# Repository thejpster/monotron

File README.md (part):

# Monotron.

> A simple 1980's home computer style application for the Tiva-C Launchpad

## The Monotron is no more

Monotron was fun, but it was only ever a tech demo rather than something we could build on. Check out <https://github.com/neotron-compute/> for our new family of ARM-based, Rust-powered home computers. 

## Introduction

Monotron is powered by a Texas Instruments TM4C123 microcontroller, containing
an ARM Cortex-M4 core and a number of peripherals. This processor was chosen
because it is available on an inexpensive dev-kit - the Tiva-C Launchpad - and
I happened to have some lying around. The challenge I set myself was, how much
can you squeeze out of this tiny CPU? And can you do it all in pure-Rust?

[See Monotron in Action!](https://www.youtube.com/watch?v=7x_92PXKSN4)

## The Future

Monotron has been replaced by the [Neotron 32](https://github.com/neotron-compute/Neotron-32-Hardware), part of the [Neotron family](https://neotron-compute.github.io). All future work will happen under the Neotron banner, and this repo is in archive mode.

## Features

* 800x600 8-colour VGA output
* 32 KiB SRAM (24 KiB usable for applications)
* 256 KiB Flash ROM
* Choice of low-memory 48x36 text display mode or full 384x288 bitmap graphics mode
* 8-bit mono audio output with 3 channel, 4 waveform synthesiser
* USB Serial I/O
* Atari 9-pin joystick interface
* Simple command-line interface
* I2C expansion interface
* Loadable apps
* Battery backed real-time clock*
* 25-pin IBM PC style parallel printer port*
* MIDI In, Out and Through*
* PS/2 Keyboard and Mouse*
* RS-232 Serial port*
* Watch this space!

 _* Requires additional hardware, included on the [Monotron PCB](#monotron-pcb)_

## Video

Monotron generates an 800x600 VGA video signal at 60 Hz using three SPI
peripherals and a timer to generate the horizontal sync signals. It can do
this because the VGA signal has a pixel clock of 40 MHz and the Tiva-C
Launchpad's TM4C123 CPU runs at 80 MHz. We save on the number of pixels we
have to push through the SPIs by running at half-resolution horizontally
(giving 400x600), which also halves the pixel clock to 20 MHz. I did try 40
MHz mode and it didn't work.

Monotron has two 'modes' it can display on this VGA output.

### Text Mode

Text Mode has a 48 character by 36 line display. Each character cell is 8
pixels wide and 16 pixels high and can take any character from the 8-bit [MS-
DOS Code Page 850](https://en.wikipedia.org/wiki/Code_page_850) character set,
and can have any foreground and background colour from the supported set:

* White
* Red
* Yellow
* Green
* Cyan
* Blue
* Magenta
* Black

The text buffer takes up `48 x 36 x 2 = 3,456` bytes of SRAM.

The built-in font is taken from
[FreeBSD](http://web.mit.edu/freebsd/head/share/syscons/fonts/cp850-8x16.fnt).
There's also a second font which implements Teletext block graphics (or
'sixels').

Any line of text can be displayed in "double height" mode, showing either the
top-half or bottom-half.

Finally, the display is framed with an 8 pixel border at the sides and a 12
pixel border at the top and bottom, to make everything fit neatly and to help
with any minor overscan issues if you use an actual CRT monitor.

### Graphics Mode

Graphics Mode can be enabled and disabled at run-time. It's not enabled by
default because bitmap graphics take up a lot of RAM!

You can attach a 1-bit-per-pixel graphics buffer that is some multiple of 384
pixels (i.e. 384 bits or 48 bytes) long. This buffer is displayed using line-
doubling (i.e. every line is shown twice) so you can go up to 384x288
resolution maximum, which will fill the screen. Each bit from the bitmap is
coloured according to the text cell (see above) it sits on top of, much like a
ZX Spectrum. A full-screen bitmap therefore uses the 3,456 bytes of SRAM from
text-mode plus an additional `384x288 / 8 = 13,824` bytes of SRAM.

## Compiling

You will need to build using Rust Nightly, as we need various experimental
features for Embedded development that are not yet available in Stable.

```
$ rustup toolchain install nightly
$ git clone https://github.com/thejpster/monotron.git
$ cd monotron
$ rustup override set nightly
$ rustup target add thumbv7em-none-eabihf
$ cargo build --release
```

To program the board, you can use lm4flash:

```
$ cargo build --release
$ arm-none-eabi-objcopy -O binary ./target/thumbv7em-none-eabihf/release/monotron ./target/thumbv7em-none-eabihf/release/monotron.bin
$ lm4flash ./target/thumbv7em-none-eabihf/release/monotron.bin
```

Or you can debug in GDB (which will automatically load the program first):

```
$ openocd
<switch to a different terminal>
$ cargo run --release
```

OpenOCD should read our `openocd.cfg` file, which directs it to use the
correct configuration. You may need to run `sudo openocd` if your user doesn't
have permission to open the USB device.

To exit GDB, you may need to press Ctrl-C multiple
times, as it seems it can get a bit stuck.

## Connecting

You have two options when running a Monotron.

1. You can take a bare Tiva-C Launchpad and wire up various connectors using
   the pin-outs in the following sections.
2. You can skip all that make yourself a [Monotron PCB](#monotron-pcb)!

### VGA

Your VGA connector requires five wires:

* Pin 1: Red - connect to PF1 via a 330 Ohm resistor.
* Pin 2: Green - connect to PB7 via a 330 Ohm resistor.
* Pin 3: Blue - connect to PD3 via a 330 Ohm resistor.
* Pin 5: Ground - connect to GND
* Pin 6: Red Return - connect to GND
* Pin 7: Green Return - connect to GND
* Pin 8: Blue Return - connect to GND
* Pin 13: H-Sync - connect to PB4
* Pin 14: V-Sync - connect to PB5

I'm using this arrangement using random resistors I found on my desk, and it
works for me (although the picture is a bit dim, as it actually produces about
0.6V peak rather than 0.7V):

```
-----+
     |     +------+ 330 Ohm        Co-ax in the VGA cable
PB7 o+-----|      |------------(o)==================)+
     |     +------+                                  |
-----+                                               |
                                                    +-+
                                                    | |
                                                    | | 75 Ohm
                                                    | | (in Monitor)
                                                    +-+
                                                     |
                                                     o
                                                    GND
```

The 330 Ohm resistor forms a resistive divider with the 75 Ohm resistor in the
monitor. This is needed to drop the 3.3V output down to 0.7V. Some monitors
are more tolerant of over voltage than others. The higher the resistor you
use, the less current you pulling out of the GPIO pin (we're just over 8mA
currently, which is a bit high) but the lower the voltage the monitor will see
and the dimmer your picture will be. Conversely if you lower the resistor,
more current will flow but it'll be a brigher picture. I'd save your chip from
damage and just wind the brightness control up!

Obviously only one channel is shown above - wire up the blue and red channels
in exactly the same fashion. Finally, don't forget to keep your wires short!
You will have noise if you try and send a 20 MHz signal down 10cm of
unshielded wire.

In a perfect world, your board would offer a 75 ohm source impendance matching
the monitor's 75 ohm impedance, to reduce reflections, but at this resolution
it doesn't seem to matter. If you want do do that, you'll need to make a
resistive divider to drop the 3.3V to 1.4V, and then feed that through a
high-bandwidth (>20 MHz) unity-gain amplifier, with a 75 ohm resistor on the
output. The pair of 75 ohm resistors will then drop the 1.4V to 0.7V in the
monitor.

### UART

Monotron primarily uses UART0, which is converted to USB Serial by the
on-board companion chip on the Tiva-C Launchpad. Connect with your favourite
Serial terminal at 115,200bps, then send UTF-8 characters and they'll get
converted to virtual keyboard input, allowing you to drive the Monotron.

There's also a second UART (UART1), which has RTS/CTS hardware handshaking
lines connected (but not DSR, DTR or RI). On the Monotron PCB these are
brought out to pin header J8. By fitting six jumpers on this header, the
on-board MAX3232 level shifter is activated, driving RS-232 signals on the
DE9M connector, J12. This connector is wired as [Data Terminal
Equipment](https://en.wikipedia.org/wiki/Data_terminal_equipment) or _DTE_ (as
opposed to [Data Communications
Equipment](https://en.wikipedia.org/wiki/Data_circuit-terminating_equipment)
or _DCE_). This means that Monotron transmits data on DE9 pin 3, and it's
designed to connect to Serial AT modems or other peripherals. Other computers
(like an old IBM PC) and even USB to RS-232 adaptors are most likely wired DTE
and so to connect one to the Monotron you'll most likely need a [null-modem
cable](https://en.wikipedia.org/wiki/Null_modem) (one that swaps pins 3 + 4
and pins 7 + 8).

Bonus points to the first person to write a BBS program for Monotron that lets
you dial up on a 56k modem.

Extra bonus points to the first person to write an xmodem file transfer
program so you can transfer files from SD card over RS-232 to an xmodem
utility on your old MS-DOS 3.3 IBM PC.

_Note: The Joystick connector looks the same as the RS232 connector - don't
mix them up!_

On the Monotron PCB, a third UART (UART3) is routed through various
opto-isolators to the MIDI In and MIDI Out ports. The MIDI Through port just
repeats everything received on the MIDI In port.

Finally, also on the Monotron PCB, a fourth UART (UART7) connects to a 5V
AtMega48 which is used as an I/O expander. This microcontroller drives two
PS/2 ports (one for keyboard, one for the mouse) as well as a full IBM
PC-style 25-pin parallel printer port.

| Launchpad Pin | Tiva-C Pin | External Pin | Function (from Monotron's point of view) |
|---------------|------------|--------------|---------------|
| N/A           | PA0        | N/A          | USB Serial Rx |
| N/A           | PA1        | N/A          | USB Serial Tx |
| J4.8          | PD6        | J12 pin 3    | RS-232 Tx     |
| J4.9          | PD7        | J12 pin 2    | RS-232 Rx     |
| J4.10         | PF4        | J12 pin 7    | RS-232 RTS    |
| J3.2          | GND        | J12 pin 8    | RS-232 CTS    |
| J4.6          | PC6        | J11 pin 4/5  | MIDI In       |
| J4.7          | PC7        | J9 pin 4/5   | MIDI Out      |
| N/A           | N/A        | J10 pin 4/5  | MIDI Through  |

### Audio

Monotron can generate 8-bit audio output using PWM on pin PE4. I use the
[monotron- synth](https://github.com/thejpster/monotron-synth) which has a
three-channel wavetable synthesiser which can bleep and bloop with square
waves, sine waves, sawtooth waves and generate white noise.

You'll need to run the pin through a low-pass filter to remove the noise, and
connect it to an amplifier as the GPIO pin won't really supply much current.

| Launchpad Pin | Tiva-C Pin | TRS          | Function  |
|---------------|------------|--------------|-----------|
| J1.5          | PE4        | Ring/Tip     |Audio Left |
| J1.6          | PE5        | Tip          |Audio Right|
| J3.2          | GND        | Sleeve       |Common     |

Currently audio only comes out as Mono on PE4 (Left). If this is a problem for
your amplifier, setting jumper J1 on the PCB to 1-2 allows you to route Audio
Left to Sleeve as well as Tip. Setting J1 to 2-3 enables stereo support,
should that ever get developed.

### Joystick

There are five active-low inputs corresponding to Up, Down, Left, Right and
Fire. You can connect these inputs to a standard Atari or Commodore 9-pin
Joystick as follows:

| Launchpad Pin | Tiva-C Pin | Joystick Pin | Function |
|---------------|------------|--------------|----------|
| J3.8          | PE2        | 1            | Up       |
| J3.9          | PE3        | 2            | Down     |
| J4.8          | PD6        | 3            | Left     |
| J4.9          | PD7        | 4            | Right    |
| J4.10         | PF4        | 6            | Fire     |
| J3.2          | GND        | 8            | Ground   |

A Sega Master System (tm) controller should work, except you'll only be able
to use Button 1 not Button 2. A Sega Mega Drive (tm) controller probably won't
work because it has more buttons than there are pins, and so uses a 5V powered
multiplexer to select between the two banks of buttons. 15-pin Analog PC
joysticks won't work either.

### SD Card

You can load programs and data from an SD card, from the first Primary MBR
(standard old-style MS-DOS) partition, formatted as either FAT16 or FAT32. Use
a standard SD Card SPI breakout adaptor, connected up as follows:

| Launchpad Pin | Tiva-C Pin | Function     |
|---------------|------------|--------------|
| J2.10         | PA2        | Clock        |
| J2.9          | PA3        | Chip Select  |
| J2.8          | PA4        | MISO/Data Out|
| J1.8          | PA5        | MOSI/Data In |

SD cards operate at 3.3v so no level shifters are required, but many cards
will require a 47k (well, between 10k and 100k) pull-up to 3.3v on all four
data pins. If you don't use these pull-ups, the pins float while the Monotron
is booting, and these fluctuations may upset the SD card, giving you random
timeouts and other spurious effects. Some cards tolerate this better than
others, so YMMV. If in doubt, just add the pull-ups (they're missing on rev
0.7.0 of the PCB, but will be on 0.8.0+).

On the console you use the `mount` command to scan the disk, then `dir` to
show the root directory contents. You can also `dload`, `ddump` and `dpage`
commands to load, hex-dump and print files to the screen. A program loaded
with `dload` can subsequently be executed with the `run` command.

### I2C

The [Monotron PCB](#monotron-pcb) has an I2C expansion header connected to
`I2C1`. The PCB can also optionally be fitted with an [Microchip
MCP7940N](https://www.microchip.com/wwwproducts/en/MCP7940N) battery-backed
real time clock chip. Driver support for this chip is TBC.

The PCB pulls-up the I2C bus to 5V through 4.7k pull-ups. On these particular
pins the TM4C123 happens to be 5V tolerant and so it simply runs the I2C pins
in open-drain mode without a level shifter.

| Launchpad Pin | Tiva-C Pin | External Pin | Function     |
|---------------|------------|--------------|--------------|
| J2.1          | GND        | J6 pin 1     | Ground       |
| J3.1          | 5V         | J6 pin 2     | 5V Power     |
| J1.10         | PA7        | J6 pin 3     | SDA          |
| J1.9          | PA6        | J6 pin 4     | SCL          |

### PS/2 Keyboard

The initial PS/2 keyboard support sort of worked, but it wasn't reliable I so
took it out again. The fundamental problem was that it's really hard to sample
a 10 to 15 kHz incoming synchronous signal without using SPI slave peripheral
(they're all in use) and while bit-bashing timing-critical video signals at 20
MHz. Either you drop random key events (leading to missing characters or stuck
keys), or the video wobbles every time a key is pressed (like a ZX81). Neither
was ideal.

On the [Monotron PCB](#monotron-pcb) I work around this issue by adding an
Atmel AtMega48 microcontroller as an I/O expander, connected to [UART](#uart)
7. Look in the [`avr_kb`](./avr_kb) folder for more information.

__Note:__ There's a bug in the 0.7.0 PCB where both PS/2 connector pinouts are
mirror image, compared to how they should be. It happened because although the
connector drawings said "Bottom View" quite clearly, I didn't pay enough
attention and assumed they were viewed from above! To use the PS/2 connectors,
they must be fitted to the underside of the PCB (i.e. opposite to all the
other connectors). This will be fixed in the next PCB revision.

### MIDI

The [Monotron PCB](#monotron-pcb) has three 5-pin DIN MIDI ports: In, Out and
Through. These are connected to UART 3.

### Parallel Printer Port

The 25-pin Parallel Printer Port is connected to the Monotron PCB's AtMega48
I/O controller. You send commands to the AtMega to get it to drive the printer
port. Currently only SPP (classic mono-directional support as found on the
original IBM PC) is planned for support. Support for the fancier EPP and ECP
modes is TBD.

## Monotron PCB

There's now a PCB! It features:

* 2x20 pin headers, to mate with the TM4C123 Launchpad (other Launchpads like
  the TM4C129 and MSP430 have not been tested and almost certainly won't work)
* 5V power jack (2.1mm barrel jack, centre +ve)
* [VGA](#vga) port (DE15HD female)
* Atari/Commodore [joystick](#joystick) port (DE9 male)
* [Micro-SD Card](#sd-card) slot
* [3.5mm stereo line out](#audio)
* [RS-232](#uart) port (DE9 male)
* 2.54mm (100 mil) jumpers to disconnect the RS232 driver and allow you to
  connect a 3.3v FTDI type TTL serial cable instead.
* [MIDI](#midi) In, Out and Through ports, with opto-isolation (5-pin DIN)
* 4-pin 2.54mm pitch (100 mil) [I2C](#i2c) expansion header (GND, 5V, SDA, SCL)
* Microchip MCP7940N I2C Real-Time Clock with battery back-up
* AtMega48 microcontroller, controlling:
  * IBM PC style parallel printer port (DB25 female)
  * PS/2 Keyboard port (6-pin mini-DIN)
  * PS/2 Mouse port (6-pin mini-DIN)

See the [pcb](./pcb) folder for Kicad files, Gerbers and PDF Schematics. If
you want to buy a PCB (with or without a kit of parts) send a message to
@therealjpster on Twitter, or via my Github e-mail. Rev 0.7.0 has some rough
edges, but I'm working on it.

## Running

When running, a simple command driven interface is presented. Commands can be
entered over serial, or using a PS/2 keyboard. Commands are split on
whitespace and then interpreted based on the left-most word. Enter the command
'help' to see a list of commands. Some commands place you in to a sub-menu -
use 'exit' to return to the previous menu.

## Loading apps

Applications can be compiled and loaded into RAM for exection. They must be
linked to run from address `0x2000_2000` and take less than 24 KiB for all
code and data combined. See the table below:

| Address     | Length  | Description  |
|-------------|---------|--------------|
| 0x0000_0000 | 256 KiB | OS Code      |
| 0x2000_0000 | 8 KiB   | OS Data      |
| 0x2000_2000 | 24 KiB  | Application  |

The first four bytes of the image must be the address of the start function,
with prototype `fn start(const struct callbacks_t* callbacks) -> int32`. Apart
from that, applications are free to apportion the remaining 24,572 bytes as
they see fit.

*Note:* The application does not need to provide a stack region - the Monotron
ROM will handle that using the system stack.

The callback structure supplied to the application's entry function is defined
in `api.rs`, but in C looks like:

```C
struct callbacks_t {
    int32_t (*putchar)(void* p_context, char ch);
    int32_t (*puts)(void* p_context, const char*);
    int32_t (*readc)(void* p_context);
    void (*wfvbi)(void* p_context);
    int32_t (*kbhit)(void* p_context);
    void (*move_cursor)(void* p_context, unsigned char row, unsigned char col);
    int32_t (*play)(void* p_context, uint32_t frequency, uint8_t channel, uint8_t waveform, uint8_t volume);
    void (*change_font)(void* p_context, uint32_t mode, const void* p_font);
    uint8_t (*get_joystick)(void* p_context);
    void (*set_cursor_visible)(void* p_context, uint8_t visible);
};
```

The C functions exported to the apps are:

* `puts` - print an 8-bit string (certain escape sequences are understood).
  Note that unlike the C routine of the same name, this function does not
  append a newline automatically. It is more like `fputs(s, stdout)`.
* `putchar` - print an 8-bit character
* `readc` - blocking wait for keyboard/serial input
* `wfvbi` - Wait For next Vertical Blanking Interval
* `kbhit` - return 1 if a key has been pressed (and so `readc` won't block),
  else return 0
* `move_cursor` - move the cursor to change where the next print goes
* `play` - play a note on one of the synthesizer channels
* `change_font` - changes the font used on screen to the normal CodePage 850,
  the Teletext font, or a custom font supplied by the application.
* `get_joystick` - returns the current state of the joystick input. Bits 0-4
  correspond to Fire, Right, Left, Down and Up respectively.
* `set_cursor_visible` - Pass 0 to disable the `_` cursor, or non-zero to enable it.

You can use the `upload` Python script in this repo to upload binary images
into RAM, or you can use the `dload` to load them from SD card.

See [monotron-apps](https://github.com/thejpster/monotron-apps) for example
apps which will run from Monotron's RAM, along with a wrapper which makes
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
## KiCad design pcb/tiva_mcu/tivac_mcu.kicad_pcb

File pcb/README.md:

# Monotron Printed Circuit Board

This is a design for a PCB for the Monotron, to help make implementations easier to build and less fragile. It's designed using [KiCad](http://kicad-pcb.org/).

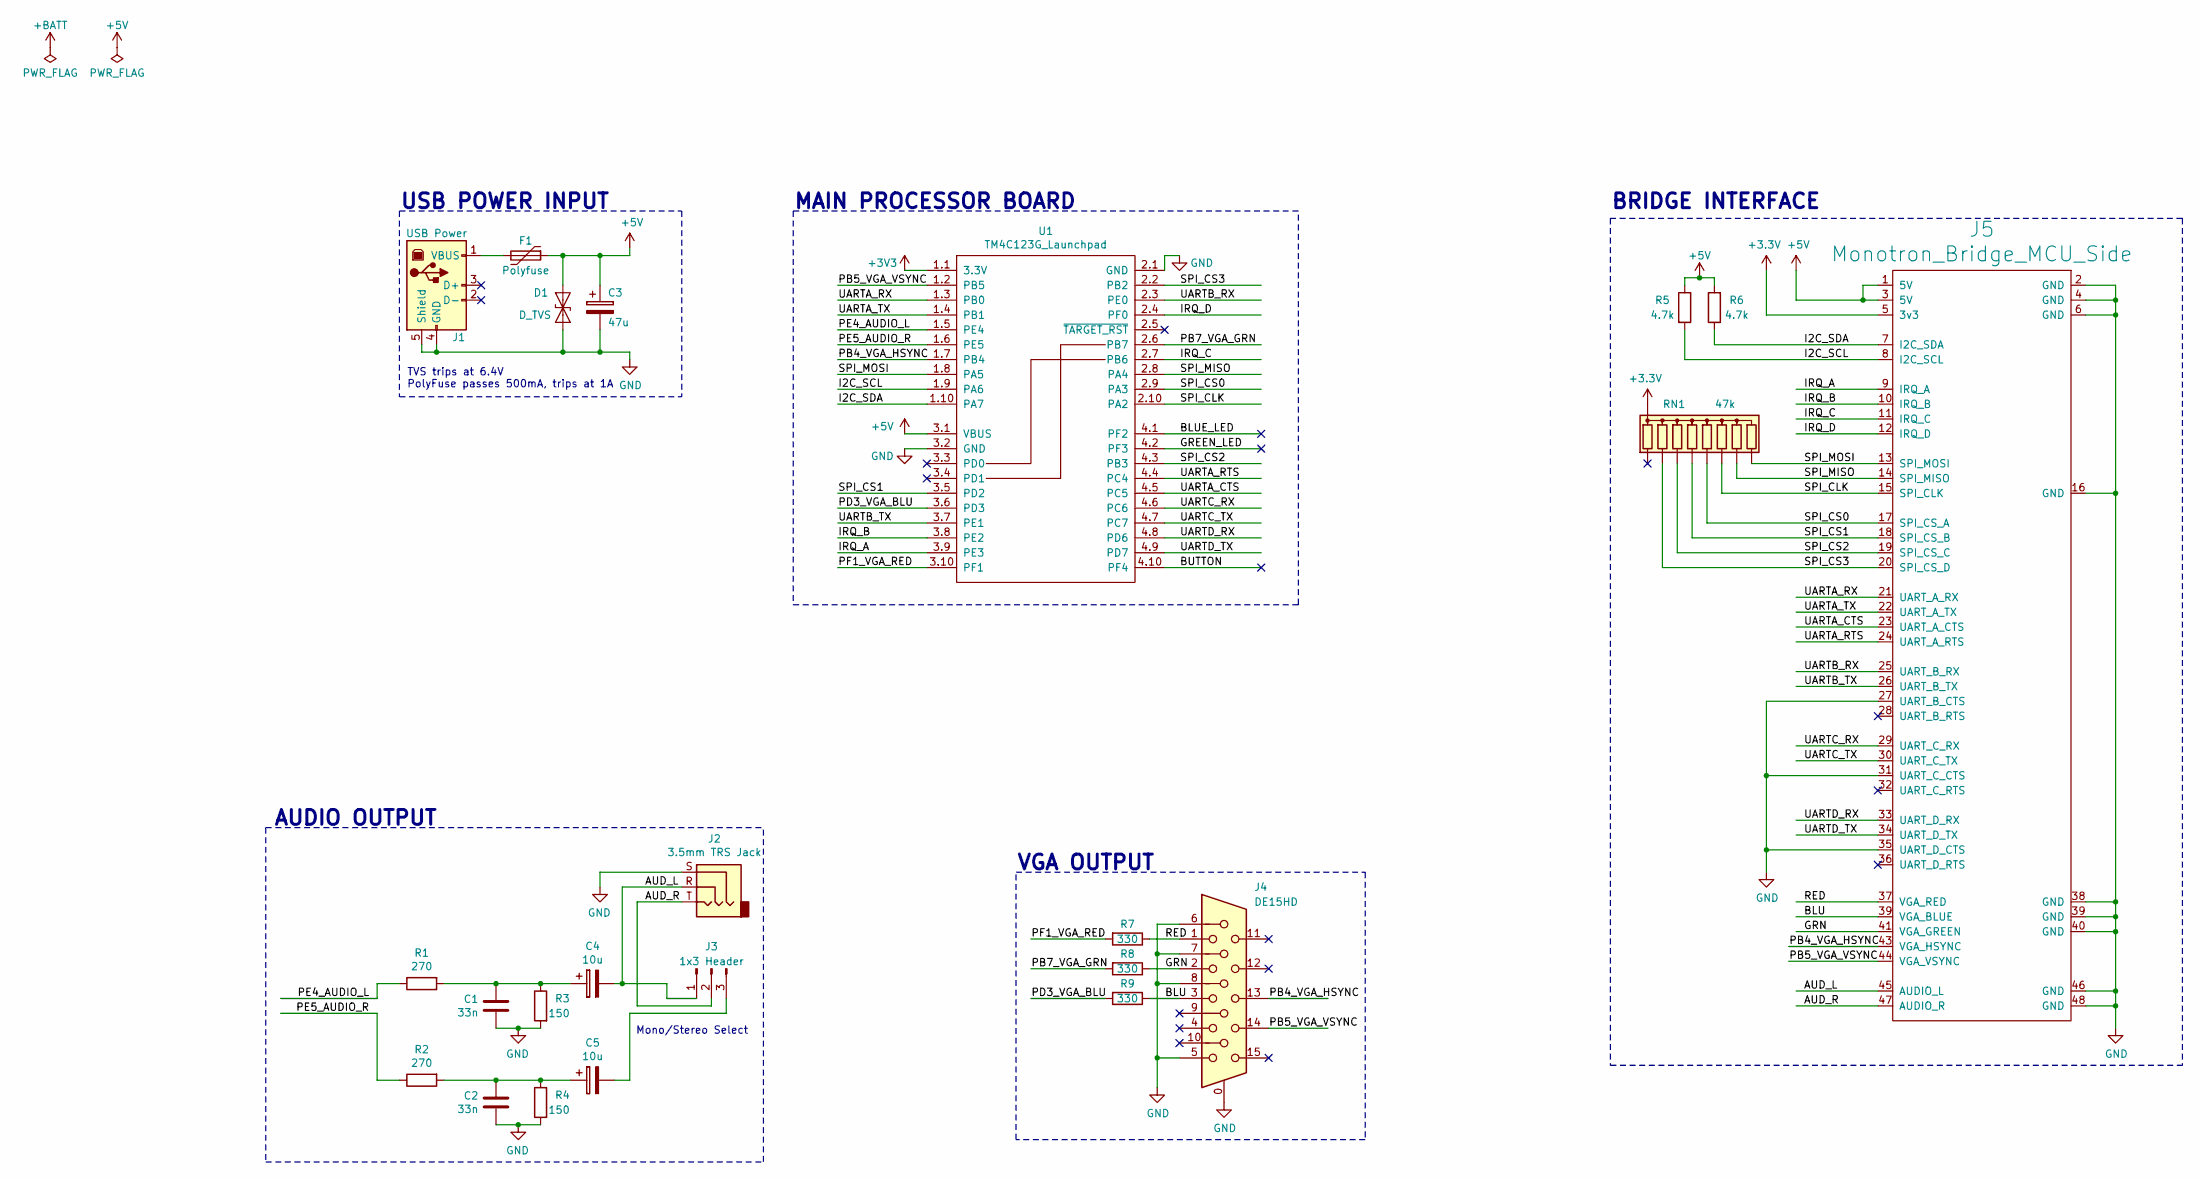
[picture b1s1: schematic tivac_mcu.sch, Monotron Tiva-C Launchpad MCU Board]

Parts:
C1, C2: 33n; C_Disc_D5.0mm_W2.5mm_P2.50mm
C3: 47u; C_Radial_D5.0mm_H5.0mm_P2.00mm
C4, C5: 10u; C_Radial_D5.0mm_H5.0mm_P2.00mm
D1: D_TVS; D_5W_P12.70mm_Horizontal; Digikey SA5.0CA-E3/54GICT-ND
F1: Polyfuse; C_Disc_D7.5mm_W4.4mm_P5.00mm; Digikey 507-2403-ND
J1: USB Power; USB_B_OST_USB-B1HSxx_Horizontal
J2: 3.5mm TRS Jack; Jack_3.5mm_CUI_SJ1-3533NG_Horizontal; Digikey CP1-3533NG-ND‎
J3: 1x3 Header; PinHeader_1x03_P2.54mm_Vertical; Digikey 609-3504-ND‎
J4: DE15HD; DSUB-15-HD_Female_Horizontal_P2.29x1.98mm_EdgePinOffset8.35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; Digikey 609-5181-ND
J5: Monotron_Bridge_MCU_Side; PinSocket_2x24_P2.54mm_Horizontal
R1, R2: 270; R_Axial_DIN0204_L3.6mm_D1.6mm_P5.08mm_Horizontal
R3, R4: 150; R_Axial_DIN0204_L3.6mm_D1.6mm_P5.08mm_Horizontal
R5, R6: 4.7k; R_Axial_DIN0204_L3.6mm_D1.6mm_P5.08mm_Horizontal
R7, R8, R9: 330; R_Axial_DIN0204_L3.6mm_D1.6mm_P5.08mm_Horizontal
RN1: 47k; R_Array_SIP9
U1: TM4C123G_Launchpad; Launchpad_4x10; Digikey 609-6378-ND‎

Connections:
+5V: C3.1, D1.1 (A1), F1.1, J5.1 (5V), J5.3 (5V), R5.1, R6.2, U1.3.1 (VBUS)
/AUD_L: C4.2, J2.R, J3.1, J5.45 (AUDIO_L)
/AUD_R: J2.T, J3.2, J5.47 (AUDIO_R)
/BLUE_LED: U1.4.1 (PF2)
/BUTTON: U1.4.10 (PF4)
/GREEN_LED: U1.4.2 (PF3)
/GRN: J4.2, J5.41 (VGA_GREEN), R8.1
/I2C_SCL: J5.8 (I2C_SCL), R5.2, U1.1.9 (PA6)
/I2C_SDA: J5.7 (I2C_SDA), R6.1, U1.1.10 (PA7)
/IRQ_A: J5.9 (IRQ_A), U1.3.9 (PE3)
/IRQ_B: J5.10 (IRQ_B), U1.3.8 (PE2)
/IRQ_C: J5.11 (IRQ_C), U1.2.7 (PB6)
/IRQ_D: J5.12 (IRQ_D), U1.2.4 (PF0)
/PB4_VGA_HSYNC: J4.13, J5.43 (VGA_HSYNC), U1.1.7 (PB4)
/PB5_VGA_VSYNC: J4.14, J5.44 (VGA_VSYNC), U1.1.2 (PB5)
/PB7_VGA_GRN: R8.2, U1.2.6 (PB7)
/PD3_VGA_BLU: R9.2, U1.3.6 (PD3)
/PE4_AUDIO_L: R1.1, U1.1.5 (PE4)
/PE5_AUDIO_R: R2.1, U1.1.6 (PE5)
/PF1_VGA_RED: R7.2, U1.3.10 (PF1)
/RED: J4.1, J5.37 (VGA_RED), R7.1
/SPI_CLK: J5.15 (SPI_CLK), RN1.7 (R6), U1.2.10 (PA2)
/SPI_CS0: J5.17 (SPI_CS_A), RN1.6 (R5), U1.2.9 (PA3)
/SPI_CS1: J5.18 (SPI_CS_B), RN1.5 (R4), U1.3.5 (PD2)
/SPI_CS2: J5.19 (SPI_CS_C), RN1.4 (R3), U1.4.3 (PB3~)
/SPI_CS3: J5.20 (SPI_CS_D), RN1.3 (R2), U1.2.2 (PB2)
/SPI_MISO: J5.14 (SPI_MISO), RN1.8 (R7), U1.2.8 (PA4)
/SPI_MOSI: J5.13 (SPI_MOSI), RN1.9 (R8), U1.1.8 (PA5)
/UARTA_CTS: J5.23 (UART_A_CTS), U1.4.5 (PC5)
/UARTA_RTS: J5.24 (UART_A_RTS), U1.4.4 (PC4)
/UARTA_RX: J5.21 (UART_A_RX), U1.1.3 (PB0)
/UARTA_TX: J5.22 (UART_A_TX), U1.1.4 (PB1)
/UARTB_RX: J5.25 (UART_B_RX), U1.2.3 (PE0)
/UARTB_TX: J5.26 (UART_B_TX), U1.3.7 (PE1)
/UARTC_RX: J5.29 (UART_C_RX), U1.4.6 (PC6)
/UARTC_TX: J5.30 (UART_C_TX), U1.4.7 (PC7)
/UARTD_RX: J5.33 (UART_D_RX), U1.4.8 (PD6)
/UARTD_TX: J5.34 (UART_D_TX), U1.4.9 (PD7)
unnamed: C1.1, C4.1, R1.2, R3.1
unnamed: C2.1, C5.1, R2.2, R4.1
unnamed: C5.2, J3.3
unnamed: F1.2, J1.1 (VBUS)

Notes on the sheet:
Mono/Stereo Select
MAIN PROCESSOR BOARD
VGA OUTPUT
AUDIO OUTPUT
USB POWER INPUT
TVS trips at 6.4V PolyFuse passes 500mA, trips at 1A
BRIDGE INTERFACE

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
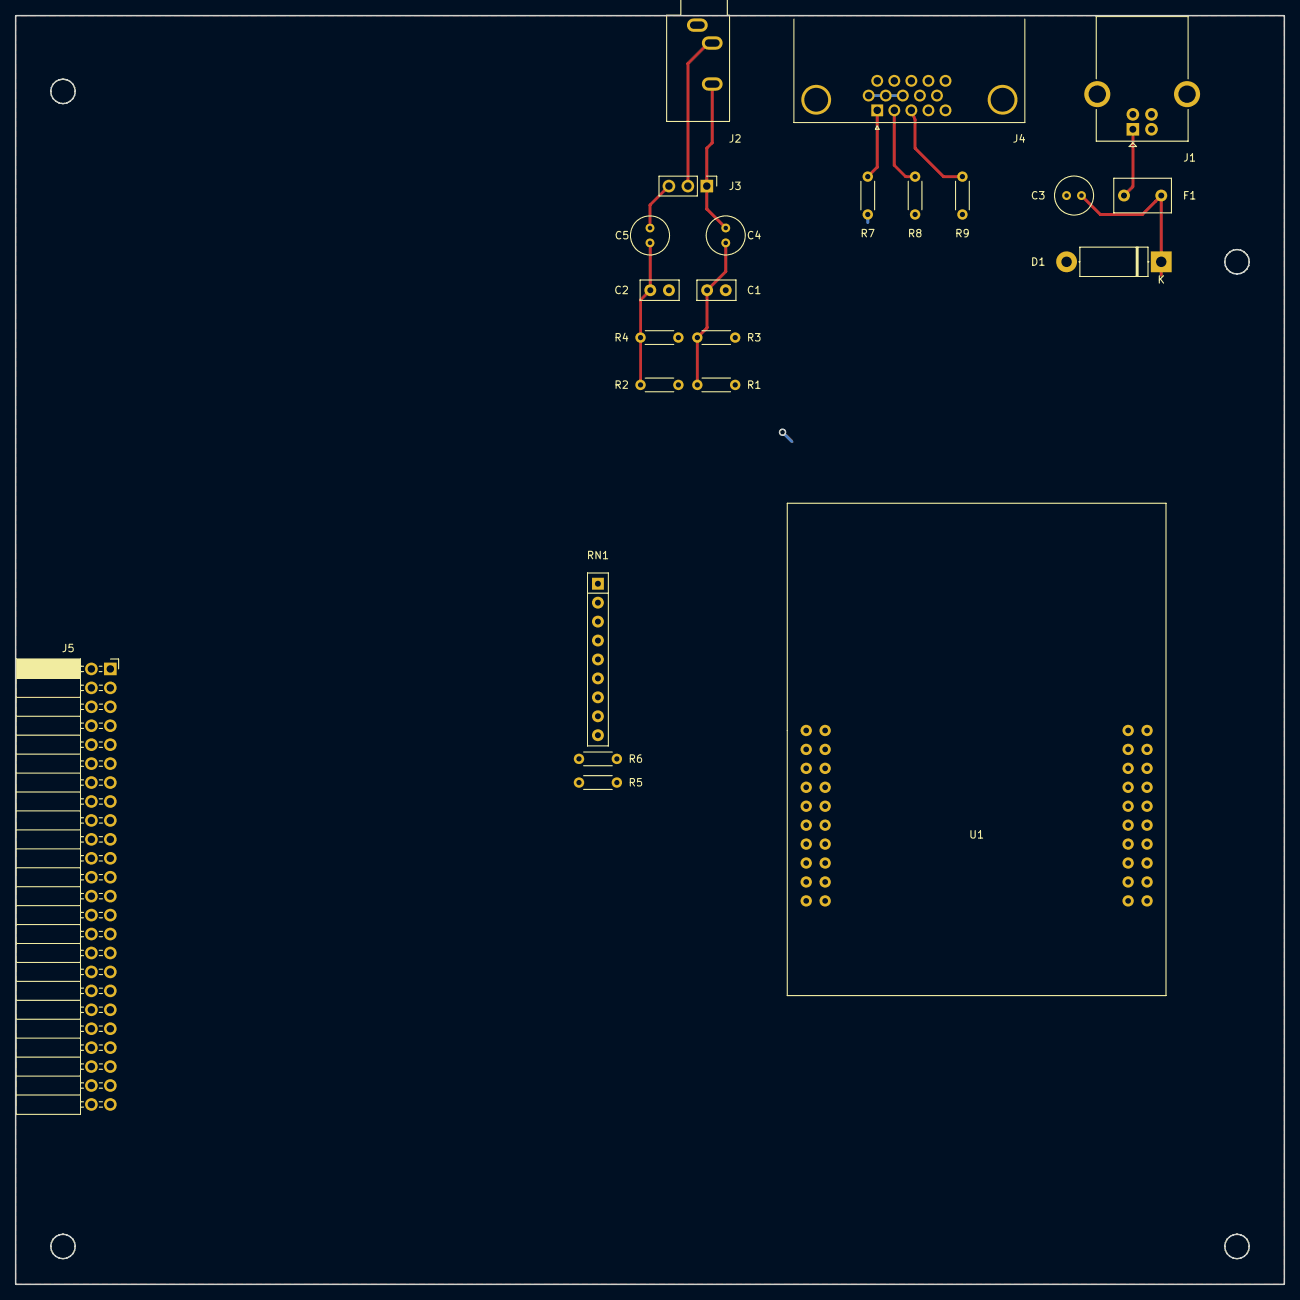
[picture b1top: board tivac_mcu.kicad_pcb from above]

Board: 2 copper layers, 170.2 x 170.2 mm, 23 parts (0 on the bottom side), 42 nets.

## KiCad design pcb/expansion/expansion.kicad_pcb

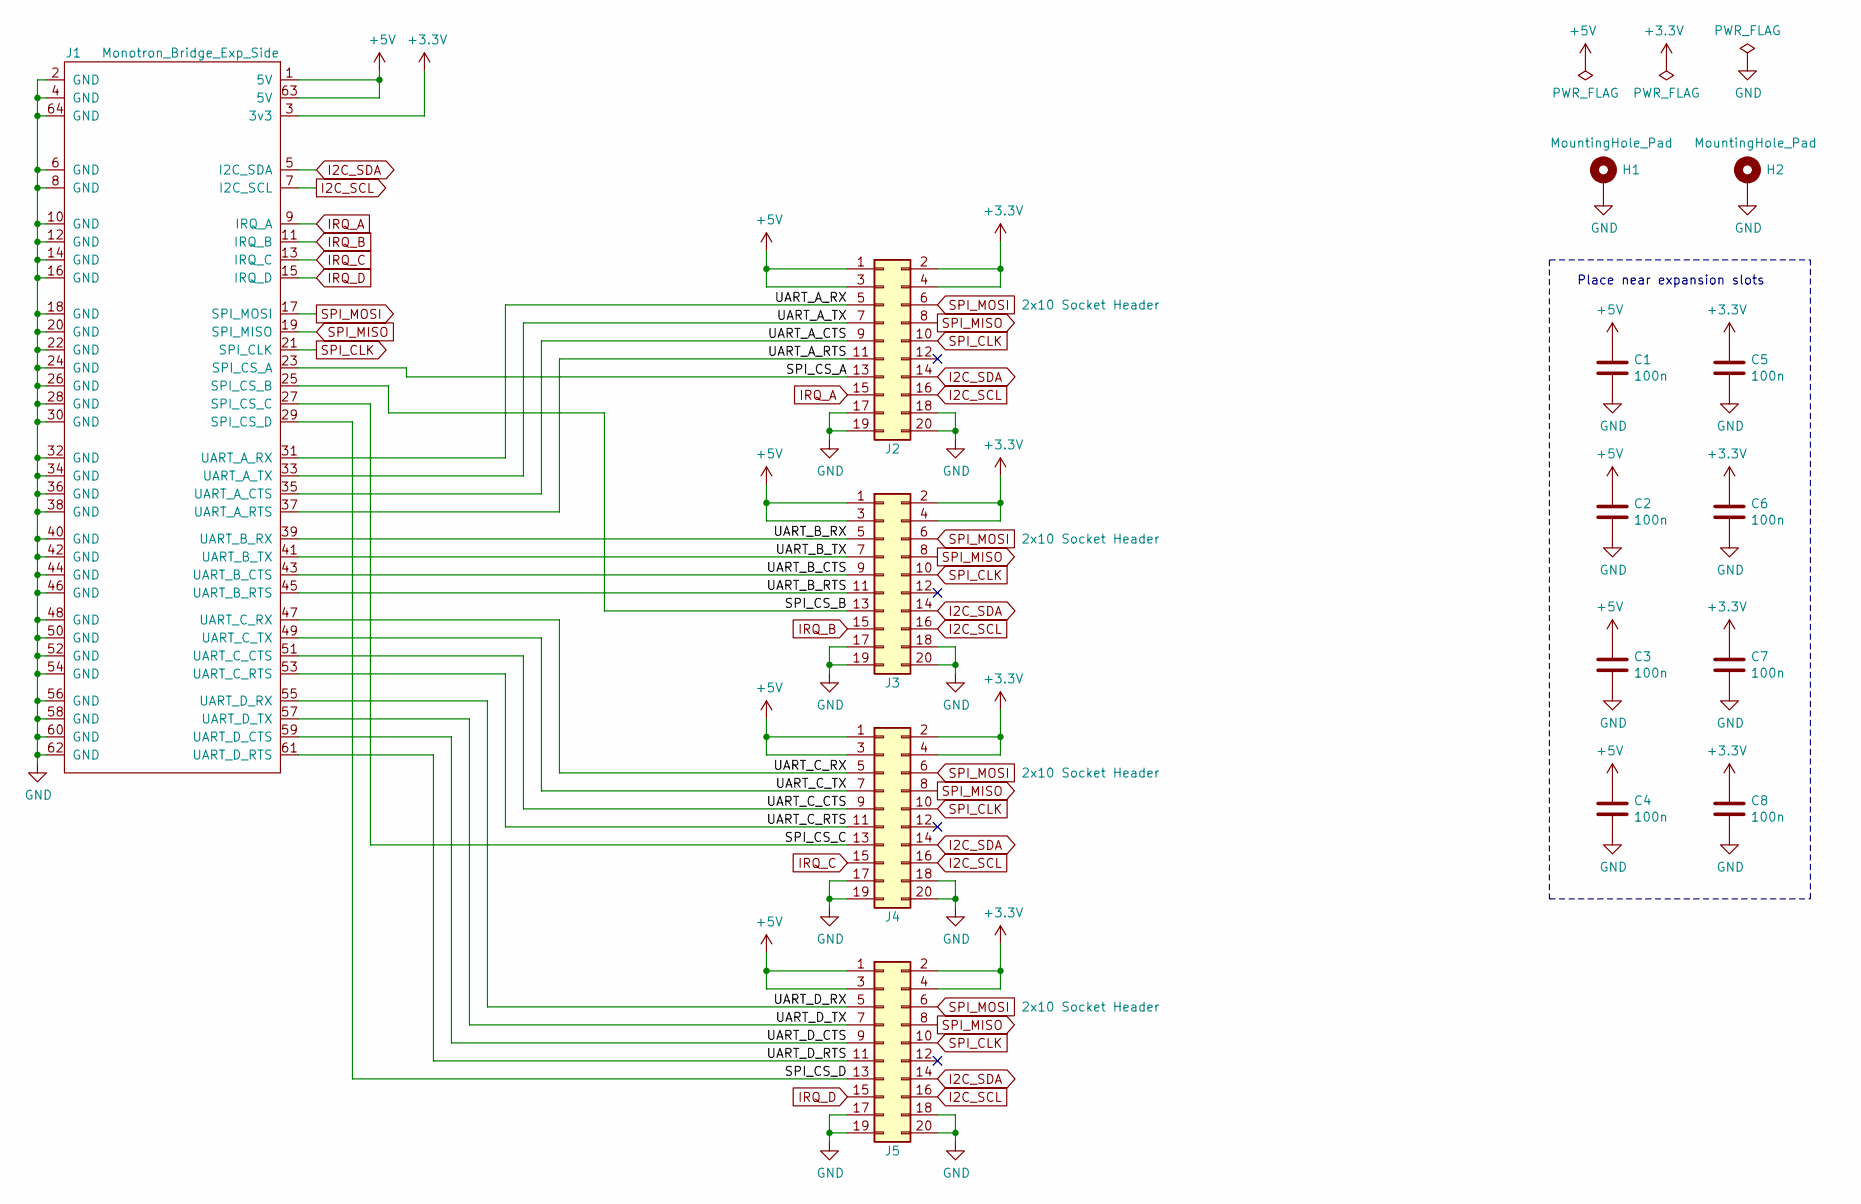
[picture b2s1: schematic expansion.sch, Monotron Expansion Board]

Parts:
C1, C2, C3, C4, C5, C6, C7, C8: 100n; C_Disc_D5.0mm_W2.5mm_P5.00mm
H1, H2: MountingHole_Pad; MountingHole_3.2mm_M3_Pad_Via
J1: Monotron_Bridge_Exp_Side; PinHeader_2x32_P2.54mm_Horizontal
J2, J3, J4, J5: 2x10 Socket Header; PinHeader_2x10_P2.54mm_Vertical

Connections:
+3V3: C5.1, C6.1, C7.1, C8.1, J1.3 (3v3), J2.2, J2.4, J3.2, J3.4, J4.2, J4.4, J5.2, J5.4
+5V: C1.1, C2.1, C3.1, C4.1, J1.1 (5V), J1.63 (5V), J2.1, J2.3, J3.1, J3.3, J4.1, J4.3, J5.1, J5.3
/SPI_CS_A: J1.23 (SPI_CS_A), J2.13
/SPI_CS_B: J1.25 (SPI_CS_B), J3.13
/SPI_CS_C: J1.27 (SPI_CS_C), J4.13
/SPI_CS_D: J1.29 (SPI_CS_D), J5.13
/UART_A_CTS: J1.35 (UART_A_CTS), J2.9
/UART_A_RTS: J1.37 (UART_A_RTS), J2.11
/UART_A_RX: J1.31 (UART_A_RX), J2.5
/UART_A_TX: J1.33 (UART_A_TX), J2.7
/UART_B_CTS: J1.43 (UART_B_CTS), J3.9
/UART_B_RTS: J1.45 (UART_B_RTS), J3.11
/UART_B_RX: J1.39 (UART_B_RX), J3.5
/UART_B_TX: J1.41 (UART_B_TX), J3.7
/UART_C_CTS: J1.51 (UART_C_CTS), J4.9
/UART_C_RTS: J1.53 (UART_C_RTS), J4.11
/UART_C_RX: J1.47 (UART_C_RX), J4.5
/UART_C_TX: J1.49 (UART_C_TX), J4.7
/UART_D_CTS: J1.59 (UART_D_CTS), J5.9
/UART_D_RTS: J1.61 (UART_D_RTS), J5.11
/UART_D_RX: J1.55 (UART_D_RX), J5.5
/UART_D_TX: J1.57 (UART_D_TX), J5.7
GND: C1.2, C2.2, C3.2, C4.2, C5.2, C6.2, C7.2, C8.2, H1.1, H2.1, J1.2 (GND), J1.4 (GND), J1.6 (GND), J1.8 (GND), J1.10 (GND), J1.12 (GND), J1.14 (GND), J1.16 (GND), J1.18 (GND), J1.20 (GND), J1.22 (GND), J1.24 (GND), J1.26 (GND), J1.28 (GND), J1.30 (GND), J1.32 (GND), J1.34 (GND), J1.36 (GND), J1.38 (GND), J1.40 (GND), J1.42 (GND), J1.44 (GND), J1.46 (GND), J1.48 (GND), J1.50 (GND), J1.52 (GND), J1.54 (GND), J1.56 (GND), J1.58 (GND), J1.60 (GND), J1.62 (GND), J1.64 (GND), J2.17, J2.18, J2.19, J2.20, J3.17, J3.18, J3.19, J3.20, J4.17, J4.18, J4.19, J4.20, J5.17, J5.18, J5.19, J5.20
I2C_SCL: J1.7 (I2C_SCL), J2.16, J3.16, J4.16, J5.16
I2C_SDA: J1.5 (I2C_SDA), J2.14, J3.14, J4.14, J5.14
IRQ_A: J1.9 (IRQ_A), J2.15
IRQ_B: J1.11 (IRQ_B), J3.15
IRQ_C: J1.13 (IRQ_C), J4.15
IRQ_D: J1.15 (IRQ_D), J5.15
SPI_CLK: J1.21 (SPI_CLK), J2.10, J3.10, J4.10, J5.10
SPI_MISO: J1.19 (SPI_MISO), J2.8, J3.8, J4.8, J5.8
SPI_MOSI: J1.17 (SPI_MOSI), J2.6, J3.6, J4.6, J5.6

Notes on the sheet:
Place near expansion slots

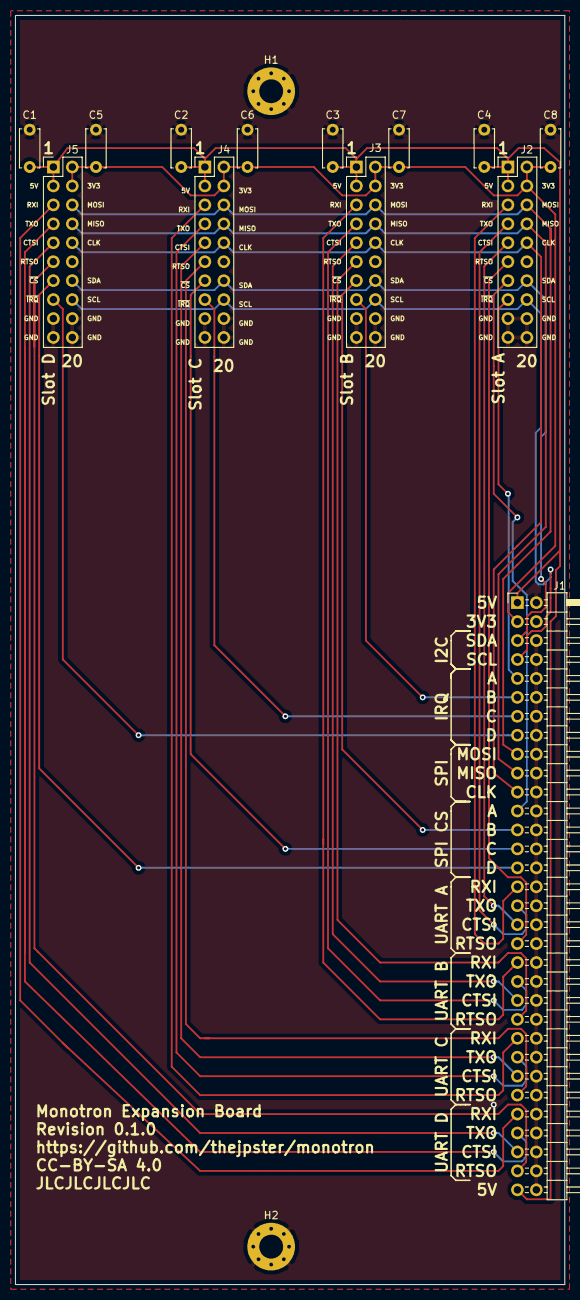
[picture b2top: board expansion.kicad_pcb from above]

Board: 2 copper layers, 73.7 x 170.2 mm, 15 parts (0 on the bottom side), 32 nets.

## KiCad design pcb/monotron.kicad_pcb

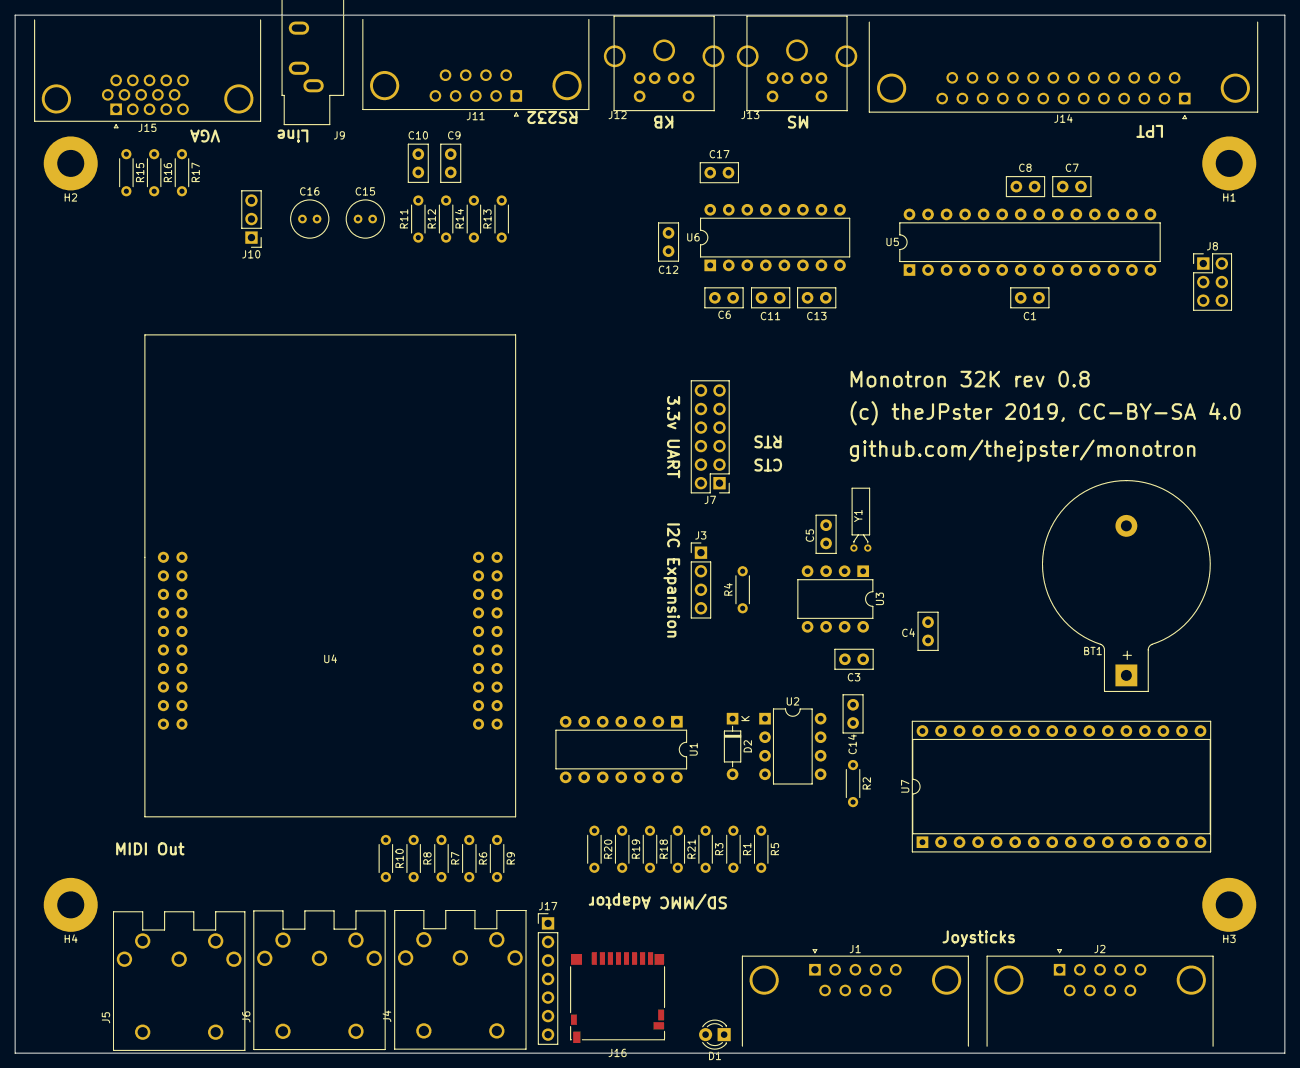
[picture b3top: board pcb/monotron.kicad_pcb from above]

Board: 2 copper layers, 174.0 x 142.2 mm, 69 parts (0 on the bottom side), 93 nets, no tracks yet.

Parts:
BT1: Battery; BatteryHolder_Keystone_103_1x20mm
C1, C3, C6, C7, C8, C14, C17: 100n; C_Disc_D5.0mm_W2.5mm_P2.50mm
C4, C5: 12p; C_Disc_D5.0mm_W2.5mm_P2.50mm
C9, C10: 33n; C_Disc_D5.0mm_W2.5mm_P2.50mm
C11, C12, C13: 470n; C_Disc_D5.0mm_W2.5mm_P2.50mm
C15, C16: 10u; C_Radial_D5.0mm_H5.0mm_P2.00mm
D1: LED; LED_D3.0mm
D2: 1N4148; D_DO-35_SOD27_P7.62mm_Horizontal
H1, H2, H3, H4: 3.7mm; MountingHole_3.7mm_Pad
J1, J2, J11: DE9M; DSUB-9_Male_Horizontal_P2.77x2.84mm_EdgePinOffset7.70mm_Hou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
J3: 1x4 Header; PinHeader_1x04_P2.54mm_Vertical
J4, J5, J6: DIN5-180; 5P180 DIN Socket
J7: 2x6 Header; PinHeader_2x06_P2.54mm_Vertical
J8: 2x3 Header; PinHeader_2x03_P2.54mm_Vertical
J9: 3.5mm TRS Jack; Jack_3.5mm_CUI_SJ1-3533NG_Horizontal
J10: 1x3 Header; PinHeader_1x03_P2.54mm_Vertical
J12, J13: Mini-DIN-6; mini-DIN 6
J14: DB25_Female; DSUB-25_Male_Horizontal_P2.77x2.84mm_EdgePinOffset7.70mm_Ho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
J15: DE15HD; DSUB-15-HD_Female_Horizontal_P2.29x1.98mm_EdgePinOffset8.35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
J16: Micro_SD_Card_Det; microSD_HC_Hirose_DM3D-SF
J17: DNF; PinHeader_1x07_P2.54mm_Vertical
R1, R3: 470; R_Axial_DIN0204_L3.6mm_D1.6mm_P5.08mm_Horizontal
R2: 10K; R_Axial_DIN0204_L3.6mm_D1.6mm_P5.08mm_Horizontal
R4, R5: 4.7k; R_Axial_DIN0204_L3.6mm_D1.6mm_P5.08mm_Horizontal
R6, R7, R8, R9, R10: 220; R_Axial_DIN0204_L3.6mm_D1.6mm_P5.08mm_Horizontal
R11, R12: 270; R_Axial_DIN0204_L3.6mm_D1.6mm_P5.08mm_Horizontal
R13, R14: 150; R_Axial_DIN0204_L3.6mm_D1.6mm_P5.08mm_Horizontal
R15, R16, R17: 330; R_Axial_DIN0204_L3.6mm_D1.6mm_P5.08mm_Horizontal
R18, R19, R20, R21: 47k; R_Axial_DIN0204_L3.6mm_D1.6mm_P5.08mm_Horizontal
U1: 74LS14; DIP-14_W7.62mm
U2: 6N138; DIP-8_W7.62mm
U3: MCP7940N-xP; DIP-8_W7.62mm
U4: TM4C123G_Launchpad; Launchpad_4x10
U5: ATmega48A-PU; DIP-28_W7.62mm
U6: MAX3232; DIP-16_W7.62mm
U7: MCP23017; DIP-32_W15.24mm_Socket
Y1: 32,768 kHz; Crystal_DS26_D2.0mm_L6.0mm_Horizontal

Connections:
+3V3: C3.1, J7.12, J16.4, J17.5, R1.1, R3.2, R18.1, R19.1, R20.1, R21.1, U3.8, U4.1.1
+5V: C1.1, C7.1, C8.1, C14.1, J3.2, J8.2, J12.4, J13.4, R4.2, R5.1, R9.1, R10.1, U1.14, U2.8, U4.3.1, U5.7, U5.20, U5.21
+BATT: BT1.1, U3.3
/KB_CLK: J12.5, U5.23
/KB_DATA: J12.1, U5.25
/LPT_ACK: J14.10, U5.4
/LPT_AUTOF: J14.14, U5.12
/LPT_BUSY: J14.11, U5.5
/LPT_D0: J14.2, U5.14
/LPT_D1: J14.3, U5.15
/LPT_D2: J14.4, U5.16
/LPT_D3_MOSI: J8.4, J14.5, U5.17
/LPT_D4_MISO: J8.1, J14.6, U5.18
/LPT_D5_SCK: J8.3, J14.7, U5.19
/LPT_D6: J14.8, U5.9
/LPT_D7: J14.9, U5.10
/LPT_ERROR: J14.15, U5.11
/LPT_INIT: J14.16, U1.10
/LPT_PE: J14.12, U5.6
/LPT_SEL: J14.13, U5.28
/LPT_SELPRIN: J14.17, U5.27
/LPT_STROBE: J14.1, U5.13
/MS_CLK: J13.5, U5.24
/MS_DATA: J13.1, U5.26
/PA2_SD_CLK: J16.5, J17.4, R19.2, U4.2.10
/PA3_SD_CS: J16.2, J17.7, R21.2, U4.2.9
/PA4_SD_MISO: J16.7, J17.2, R18.2, U4.2.8
/PA5_SD_MOSI: J16.3, J17.6, R20.2, U4.1.8
/PA6_I2C_SCL: J3.4, R4.1, U4.1.9
/PA7_I2C_SDA: J3.3, R5.2, U3.5, U3.6, U4.1.10
/PB0_U1RX: J7.10, U4.1.3
/PB1_U1TX: J7.8, U4.1.4
/PB2_INIT: U1.13, U4.2.2
/PB4_VGA_HSYNC: J15.13, U4.1.7
/PB5_VGA_VSYNC: J15.14, U4.1.2
/PB7_VGA_GRN: R16.2, U4.2.6
/PC4_U1RTS: J7.6, U4.4.4
/PC5_U1CTS: J7.4, U4.4.5
/PC6_MIDI_IN: R1.2, U1.1, U2.6, U4.4.6
/PC7_MIDI_OUT: U1.9, U4.4.7
/PD2_SD_ACT: D1.1, U4.3.5
/PD3_VGA_BLU: R17.2, U4.3.6
/PD6_JS_LEFT: J2.3, U4.4.8
/PD7_JS_RIGHT: J2.4, U4.4.9
/PE0_U7RX: U4.2.3, U5.3
/PE1_U7TX: U4.3.7, U5.2
/PE2_JS_UP: J2.1, U4.3.8
/PE3_JS_DOWN: J2.2, U4.3.9
/PE4_AUDIO_L: R11.1, U4.1.5
/PE5_AUDIO_R: R12.1, U4.1.6
/PF1_VGA_RED: R15.2, U4.3.10
/PF4_JS_FIRE: J2.6, U4.4.10
/RS232_CTS: J11.8, U6.8
/RS232_RTS: J11.7, U6.7
/RS232_RX: J11.2, U6.13
/RS232_TX: J11.3, U6.14
GND: BT1.2, C1.2, C3.2, C4.1, C5.1, C7.2, C8.2, C9.2, C10.2, C13.1, C14.2, C17.2, J2.8, J3.1, J4.2, J6.2, J7.1, J7.2, J8.6, J9.S, J11.5, J12.3, J13.3, J14.18, J14.19, J14.20, J14.21, J14.22, J14.23, J14.24, J14.25, J15.0, J15.5, J15.6, J15.7, J15.8, J16.6, J16.11, J17.3, R2.2, R13.2, R14.2, U1.7, U2.5, U3.4, U4.2.1, U4.3.2, U5.8, U5.22, U6.15
unnamed: C4.2, U3.1, Y1.1
unnamed: C5.2, U3.2, Y1.2
unnamed: C6.1, U6.1
unnamed: C6.2, U6.3
unnamed: C10.1, C16.1, R12.2, R14.1
unnamed: C11.1, U6.4
unnamed: C11.2, U6.5
unnamed: C12.1, C17.1, J7.11, U6.16
unnamed: C12.2, U6.2
unnamed: C13.2, U6.6
unnamed: C9.1, C15.1, R11.2, R13.1
unnamed: C15.2, J9.R, J10.1
unnamed: C16.2, J10.3
unnamed: D1.2, R3.1
unnamed: D2.1, J5.4, U2.2
unnamed: D2.2, R8.1, U2.3
unnamed: J4.4, R9.2
unnamed: J4.5, R6.2
unnamed: J5.5, R8.2
unnamed: J6.4, R10.2
unnamed: J6.5, R7.2
unnamed: J7.3, U6.9
unnamed: J7.5, U6.10
unnamed: J7.7, U6.11
unnamed: J7.9, U6.12
unnamed: J8.5, U5.1
unnamed: J9.T, J10.2
unnamed: J15.1, R15.1
unnamed: J15.2, R16.1
unnamed: J15.3, R17.1
unnamed: R2.1, U2.7
unnamed: R6.1, U1.6
unnamed: R7.1, U1.4
unnamed: U1.2, U1.5
unnamed: U1.3, U1.8
unnamed: U1.11, U1.12

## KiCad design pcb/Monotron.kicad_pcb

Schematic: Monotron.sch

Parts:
C1: 3.3n; C_Disc_D3.4mm_W2.1mm_P2.50mm
J1: DB15_Female_HighDensity; ICD15S13E4GX00LF
J2: Mini-DIN-6; 5749180-1
J3: AudioJack3_Ground; SJ1-3523N
J4: DB9_Male; D09P13B4PA00LF
J5: Conn_02x05_Counter_Clockwise; Pin_Header_Straight_2x05_Pitch2.54mm
R1, R2, R3: 330; R_Axial_DIN0207_L6.3mm_D2.5mm_P10.16mm_Horizontal
R4, R5: 10K; R_Axial_DIN0207_L6.3mm_D2.5mm_P10.16mm_Horizontal
R6: 2.4k; R_Axial_DIN0207_L6.3mm_D2.5mm_P10.16mm_Horizontal
U1: TivaCLaunchpad; Tiva-C Launchpad Connector

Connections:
5.0V: J2.4, J4.7, R4.2, R5.2, U1.3.01
+CLK: J2.5, J5.7, R4.1
+DATA: J2.1, J5.9, R5.1
AInputPaddle: J4.9, J5.8
Audio: J5.5, R6.2
BInputPaddle: J4.5, J5.10
Blue: R3.1, U1.3.06
GND: C1.1, J1.5, J1.6, J1.7, J1.8, J2.3, J3.S, J4.8, U1.2.01
Green: R2.1, U1.2.06
H-Sync: J1.13, U1.1.07
InputTrigger: J4.6, J5.2
JoystickDown: J4.2, J5.3
JoystickLeft: J4.3, J5.4
JoystickRight: J4.4, J5.6
JoystickUp: J4.1, J5.1
unnamed: C1.2, J3.R, J3.T, R6.1
unnamed: J1.1, R1.2
unnamed: J1.2, R2.2
unnamed: J1.3, R3.2
Red: R1.1, U1.3.10
V-Sync: J1.14, U1.1.02

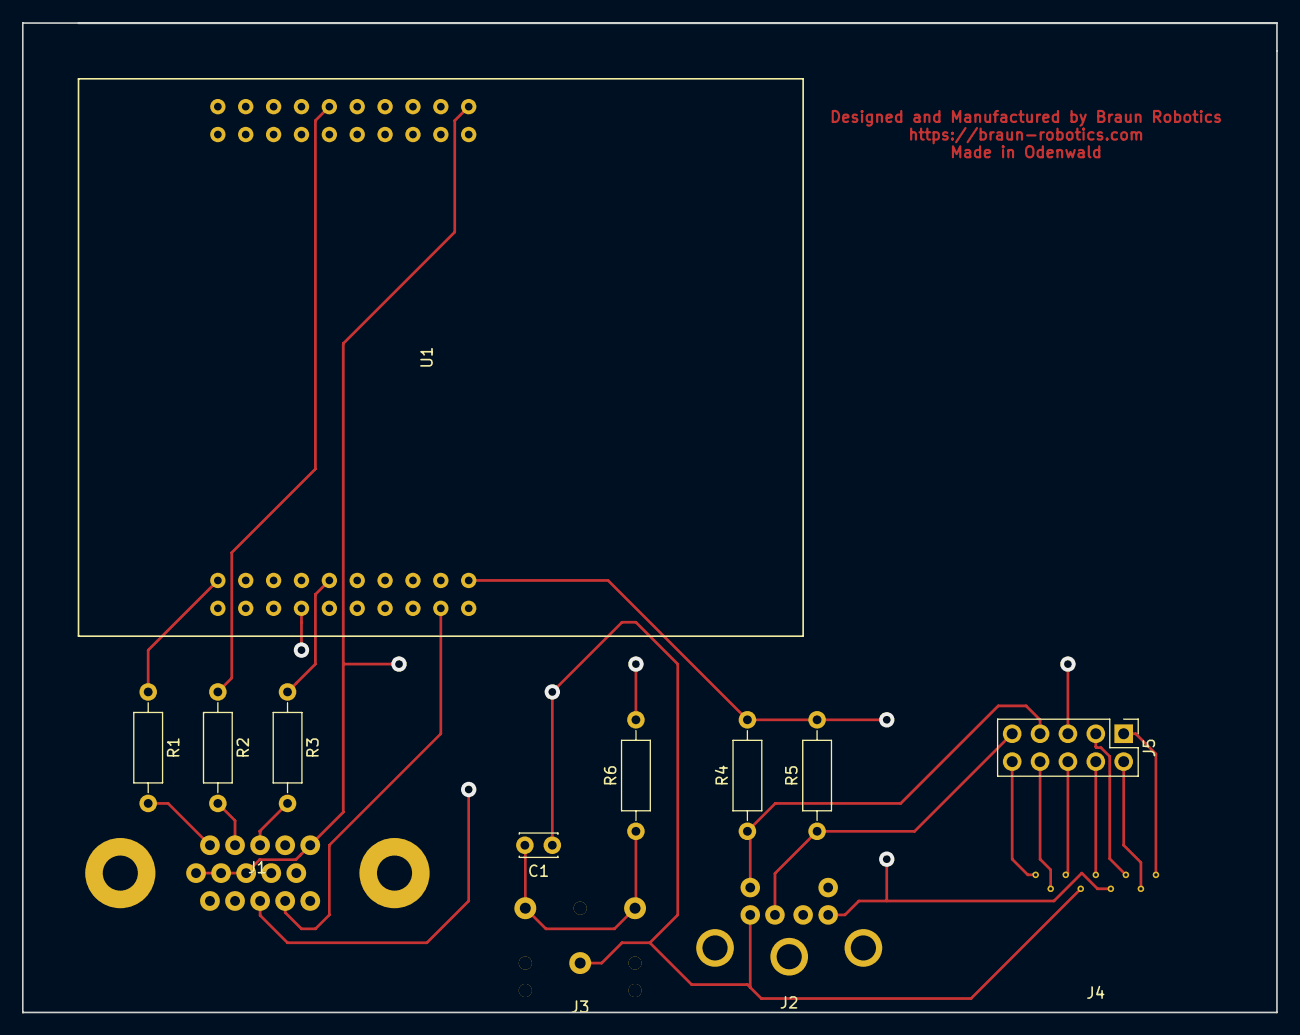
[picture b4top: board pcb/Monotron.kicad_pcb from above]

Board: 2 copper layers, 114.3 x 90.2 mm, 13 parts (0 on the bottom side), 21 nets.

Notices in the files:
README.md:
License:
Licensed under either of
- Apache License, Version 2.0 ([LICENSE-APACHE](LICENSE-APACHE) or
http://www.apache.org/licenses/LICENSE-2.0)
- MIT license ([LICENSE-MIT](LICENSE-MIT) or http://opensource.org/licenses/MIT)
at your option.
pcb/expansion/expansion.kicad_pcb:
CC-BY-SA 4.0
pcb/monotron.kicad_pcb:
Copyright (c) Jonathan 'theJPster' Pallant 2019
(c) theJPster 2019, CC-BY-SA 4.0
